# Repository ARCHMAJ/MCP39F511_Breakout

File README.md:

# MCP39F511 Breakout

[MCP39F511](https://www.digikey.com.au/product-detail/en/microchip-technology/MCP39F511-E-MQ/MCP39F511-E-MQ-ND/5323591) Energy Monitor ASIC Breakout

KiCAD model from [SnapEDA](https://www.snapeda.com/parts/MCP39F511-E/MQ/Microchip/view-part/?ref=digikey)

## Board Renders

This board is available via :

- [Tindie](https://www.tindie.com/products/whatnick/mcp39f511-breakout/)
- [OSHPark]()
- [Aisler]()
- [PCBWay]()

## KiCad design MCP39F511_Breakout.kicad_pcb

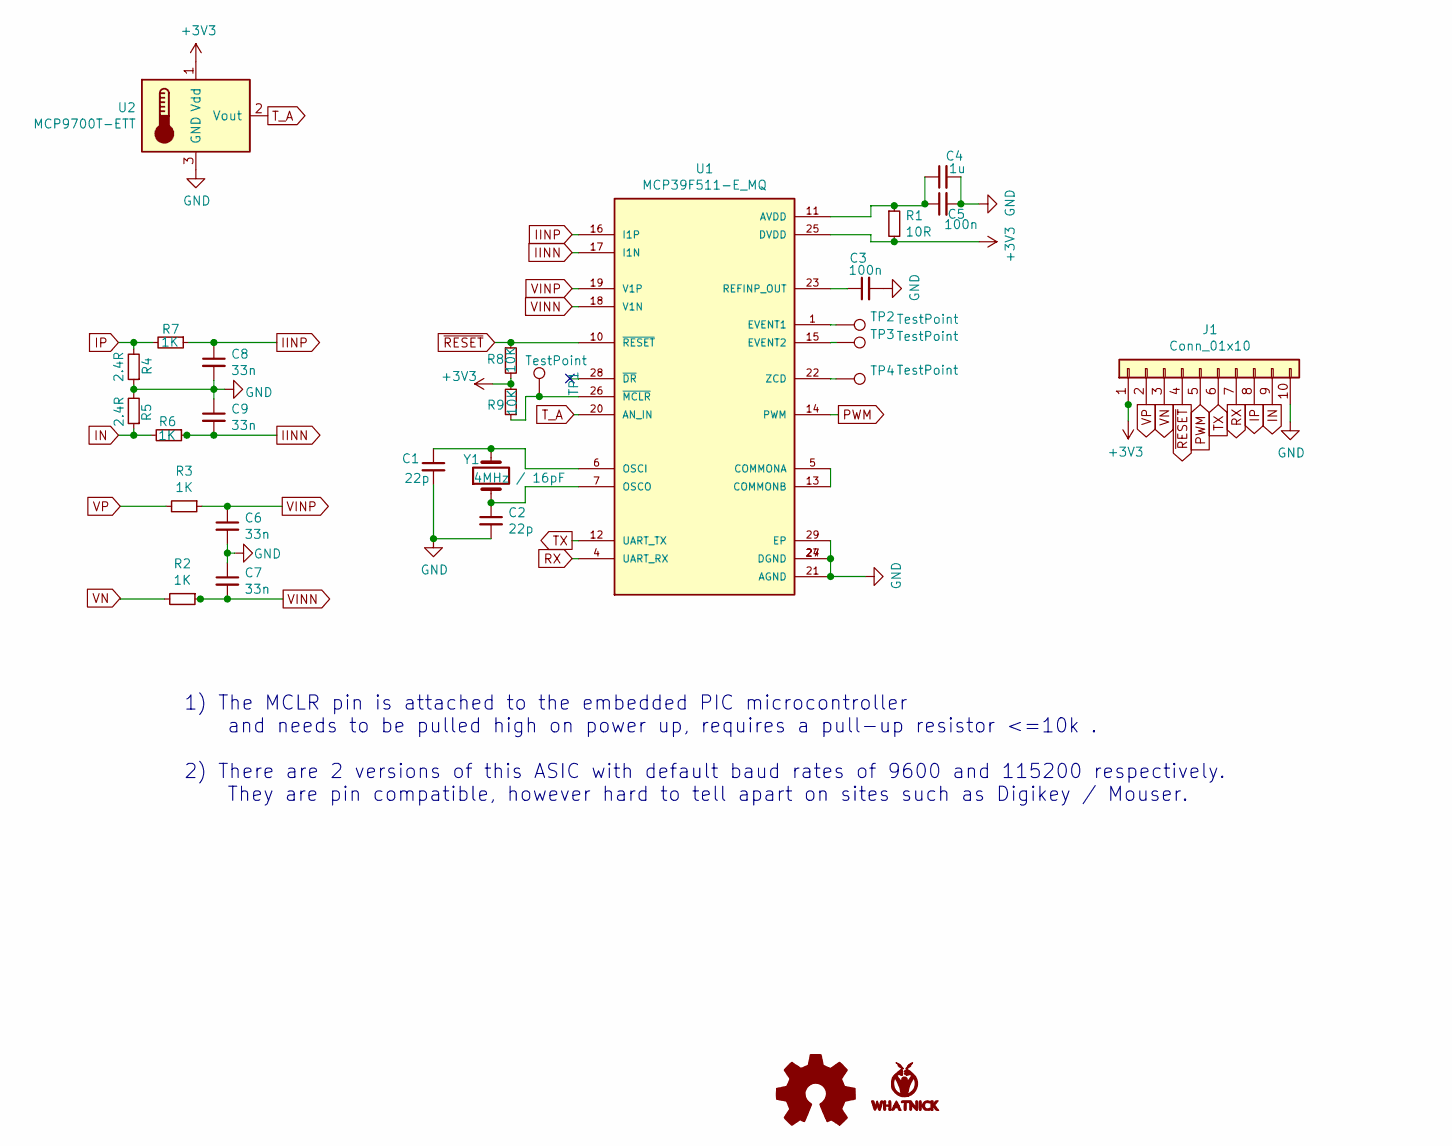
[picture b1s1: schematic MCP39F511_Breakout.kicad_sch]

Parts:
C1, C2: 22p; C_0603_1608Metric
C3, C5: 100n; C_0603_1608Metric
C4: 1u; C_0603_1608Metric
C6, C7, C8, C9: 33n; C_0603_1608Metric
J1: Conn_01x10; PinHeader_1x10_P2.54mm_Vertical
LOGO1: Logo_Open_Hardware_Small; OSHW-Logo2_7.3x6mm_SilkScreen
LOGO2: LOGO; Whatnick_logo
R1: 10R; R_0603_1608Metric
R2, R3, R6, R7: 1K; R_0603_1608Metric
R4, R5: 2.4R; R_0603_1608Metric
R8, R9: 10K; R_0603_1608Metric
TP1, TP2, TP3, TP4: TestPoint; TestPoint_Pad_D2.0mm
U1: MCP39F511-E_MQ; QFN50P500X500X100-29N; PARTREV B
U2: MCP9700T-ETT; SOT-23
Y1: 4MHz / 16pF; Crystal_SMD_HC49-SD

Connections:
+3V3: J1.1, R1.2, R8.2, R9.2, U1.25 (DVDD), U2.1 (Vdd)
GND: C1.2, C2.2, C3.2, C4.2, C5.2, C6.2, C7.1, C8.2, C9.1, J1.10, R4.1, R5.2, U1.21 (AGND), U1.24 (DGND), U1.27 (DGND), U1.29 (EP), U2.3 (GND)
IINN: C9.2, R6.1, U1.17 (I1N)
IINP: C8.1, R7.1, U1.16 (I1P)
IN: J1.9, R5.1, R6.2
IP: J1.8, R4.2, R7.2
unnamed: C1.1, U1.6 (OSCI), Y1.2
unnamed: C2.1, U1.7 (OSCO), Y1.1
unnamed: C3.1, U1.23 (REFINP_OUT)
unnamed: C4.1, C5.1, R1.1, U1.11 (AVDD)
unnamed: R9.1, TP1.1, U1.26 (~MCLR)
unnamed: TP2.1, U1.1 (EVENT1)
unnamed: TP3.1, U1.15 (EVENT2)
unnamed: TP4.1, U1.22 (ZCD)
unnamed: U1.5 (COMMONA), U1.13 (COMMONB)
PWM: J1.5, U1.14 (PWM)
RX: J1.7, U1.4 (UART_RX)
TX: J1.6, U1.12 (UART_TX)
T_A: U1.20 (AN_IN), U2.2 (Vout)
VINN: C7.2, R2.1, U1.18 (V1N)
VINP: C6.1, R3.1, U1.19 (V1P)
VN: J1.3, R2.2
VP: J1.2, R3.2
~RESET: J1.4, R8.1, U1.10 (~RESET)

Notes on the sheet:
1) The MCLR pin is attached to the embedded PIC microcontroller and needs to be pulled high on power up, requires a pull-up resistor <=10k . 2) There are 2 versions of this ASIC with default baud rates of 9600 and 115200 respectively. They are pin compatible, however hard to tell apart on sites suc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

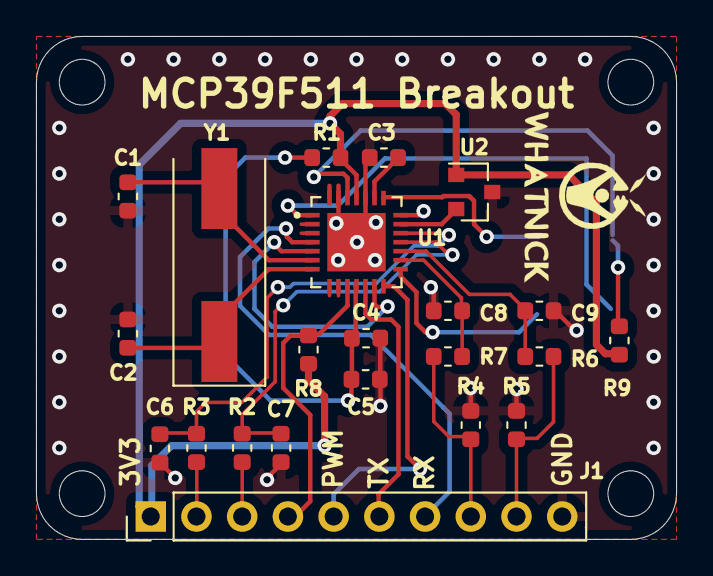
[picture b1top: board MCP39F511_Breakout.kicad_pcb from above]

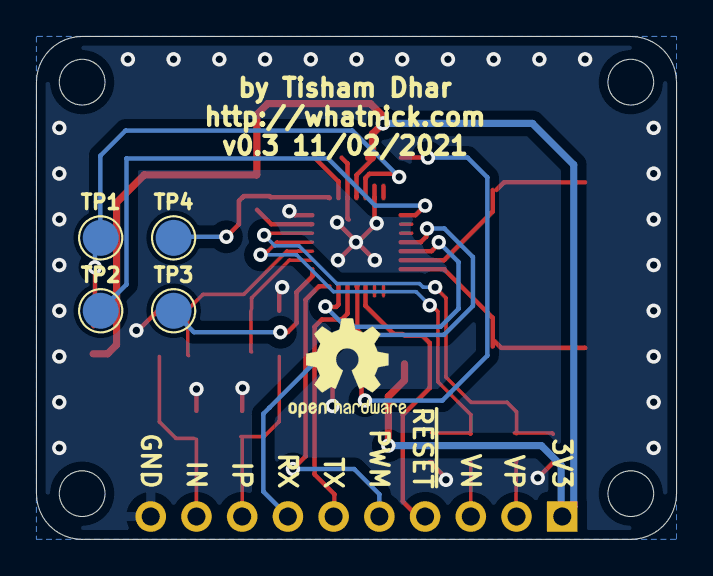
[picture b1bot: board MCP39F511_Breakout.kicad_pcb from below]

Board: 2 copper layers, 35.6 x 27.9 mm, 28 parts (5 on the bottom side), 24 nets.

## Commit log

2020-11-13 Initial import
2020-11-13 Add README
2020-11-13 Remove _
2020-11-13 PCB Edge cuts
2020-11-14 Initial complete schematic
2020-11-14 Add circuit from appnote
2020-11-14 Finish routing and silk-screens
2020-11-15 Add gerbers
2020-11-22 Do an iBOM run
2020-11-22 Do a MPN included iBOM run
2020-11-22 Update BOM
2020-11-25 Add OSHW License
2020-12-06 Add longer fillets to pads
2020-12-06 New manufacture files
2020-12-06 Footprint positions
2020-12-10 Add MCLR pullup
2020-12-10 Update BOM, positions for new pullup
2020-12-10 Schematic pdf
2020-12-12 Remove old schematic
2020-12-17 Schematic Cleanup, Notes added, PCB cleanup
2020-12-20 Upgrade to latest nightly, and squash DRC
2020-12-20 Make some silk screen enhancements
2021-01-04 PCB rerouting done
2021-01-10 Create v0.3 board
2021-01-10 Add board renders
